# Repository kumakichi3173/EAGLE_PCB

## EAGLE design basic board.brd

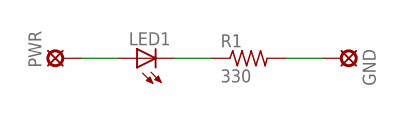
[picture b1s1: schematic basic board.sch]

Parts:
GND: LSP11
LED1: LED3MM
PWR: LSP11
R1: 330; 0207/7

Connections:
unnamed: LED1.A, PWR.MP
unnamed: LED1.K (C), R1.1
unnamed: GND.MP, R1.2

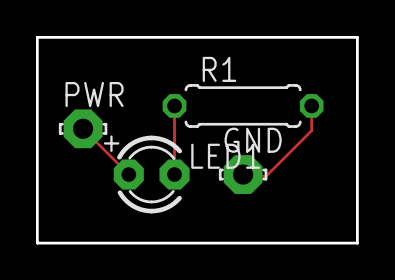
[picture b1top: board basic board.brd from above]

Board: 2 copper layers, 17.8 x 11.4 mm, 4 parts (0 on the bottom side), 3 nets.

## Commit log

2022-06-07 added basic pcb board files
2022-06-07 custom board was added (datasheet is also uploaded)
2022-06-07 added custom PCB board
    also check the datasheet
